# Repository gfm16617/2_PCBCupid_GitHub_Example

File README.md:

View this project on [CADLAB.io](https://cadlab.io/project/29834). 

# 2_PCBCupid_GitHub_Example

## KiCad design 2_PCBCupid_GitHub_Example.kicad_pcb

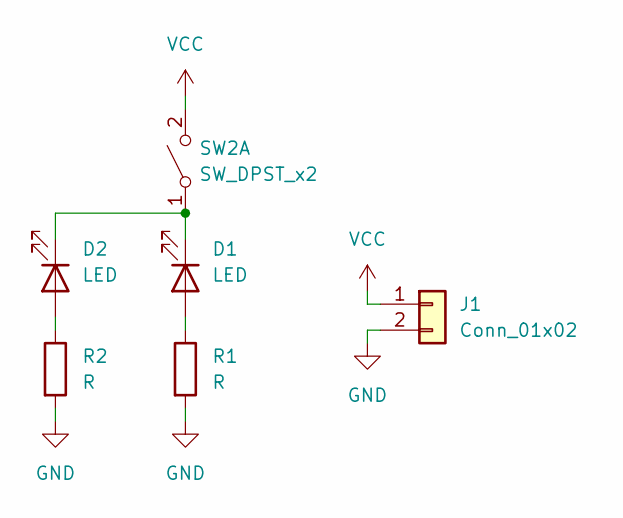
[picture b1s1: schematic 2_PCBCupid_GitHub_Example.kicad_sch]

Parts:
D1, D2: LED; LED_0805_2012Metric
J1: Conn_01x02; PinHeader_1x02_P2.54mm_Vertical_SMD_Pin1Left
R1, R2: R; R_0805_2012Metric
SW2: SW_DPST_x2; SW_Push_1P1T_NO_CK_KMR2

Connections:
GND: J1.2, R1.2, R2.2
unnamed: D1.2 (A), R1.1
unnamed: D1.1 (K), D2.1 (K), SW2.1 (A)
unnamed: D2.2 (A), R2.1
VCC: J1.1, SW2.2 (B)

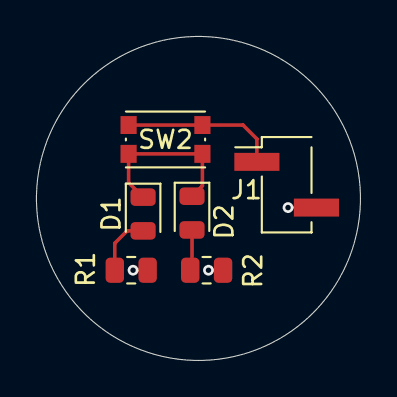
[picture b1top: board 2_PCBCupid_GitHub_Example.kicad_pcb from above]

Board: 2 copper layers, 18.0 x 18.0 mm, 6 parts (0 on the bottom side), 5 nets.

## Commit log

2026-01-04 Cupid GitHub example
2026-01-04 PCB Cupid GitHub Example files
2026-01-04 THT component added
2026-01-04 all components added to the board missing layout and routing
2026-01-04 Fixed swithc 2 schematic and pcb layout
2026-01-04 Layout completed
2026-01-04 SMD schematic and layout completed
2026-01-04 Routing completed
2026-01-04 something needs to be committed
2026-01-04 gerber files created
2026-01-04 I don't need these files
2026-01-04 check version
2026-01-04 Backlink to CADLAB.io has been added.
